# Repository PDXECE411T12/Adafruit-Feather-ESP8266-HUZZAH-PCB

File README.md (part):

<!DOCTYPE html>
<html lang="en" data-color-mode="light">
  <head>
    <meta charset="utf-8">
  <link rel="dns-prefetch" href="https://github.githubassets.com">
  <link rel="dns-prefetch" href="https://avatars0.githubusercontent.com">
  <link rel="dns-prefetch" href="https://avatars1.githubusercontent.com">
  <link rel="dns-prefetch" href="https://avatars2.githubusercontent.com">
  <link rel="dns-prefetch" href="https://avatars3.githubusercontent.com">
  <link rel="dns-prefetch" href="https://github-cloud.s3.amazonaws.com">
  <link rel="dns-prefetch" href="https://user-images.githubusercontent.com/">

  <link crossorigin="anonymous" media="all" integrity="sha512-BSy+E+S5PJuDWKcXiIXBoFJ7uJ+88y6hFdIhZpf7nf9MVNVvnJDPUaotaxFUQi8UXCLJOcGv1uifxVMc9o5DYQ==" rel="stylesheet" href="https://github.githubassets.com/assets/frameworks-052cbe13e4b93c9b8358a7178885c1a0.css" />
  
    <link crossorigin="anonymous" media="all" integrity="sha512-8Z+f0e6DBG9ZzxgV2Wf00KIGBotnuoKMOm3Rv8UbrIEoE7GWgF3QfZSZn6Mm4VUdBYSwqlvZLzeuQjojgH6lUA==" rel="stylesheet" href="https://github.githubassets.com/assets/github-f19f9fd1ee83046f59cf1815d967f4d0.css" />

  <script crossorigin="anonymous" defer="defer" integrity="sha512-8K2vvwbW+6H27Nad5ydg8PA2/aMD/LKq+EiK9s0U0hhVZxCI2tWBsYk9beAtisRw2j+Or5k2/F+6dk02nmj/PA==" type="application/javascript" src="https://github.githubassets.com/assets/environment-f0adafbf.js"></script>
    <script crossorigin="anonymous" defer="defer" integrity="sha512-gblEJf3YvaT1I3Ifn0J6OEL2Vgqq3zVla1fZ22EBfbdlAlq17e9EcuvE9InK3D/hrkh9kFJHDxGc7hXeetU45g==" type="application/javascript" src="https://github.githubassets.com/assets/chunk-frameworks-81b94425.js"></script>
    <script crossorigin="anonymous" defer="defer" integrity="sha512-TZfq2T+XE31Mcp17bGlABjjeQ/69IH2f/sBvS31c4Jua0e1O/NE+aVbQtItMM2GFlmeEm13p/zyyWGIx10jVKQ==" type="application/javascript" src="https://github.githubassets.com/assets/chunk-vendor-4d97ead9.js"></script>
  
  <script crossorigin="anonymous" defer="defer" integrity="sha512-r+GiAgjep5SyP+FNjsA/raxAAyrUmHUqN9sqy0T00pOb4D04zw6NLfs+JfGSukD34SO6nJq1KPuMyLVk36P3PA==" type="application/javascript" src="https://github.githubassets.com/assets/behaviors-afe1a202.js"></script>
  
    <script crossorigin="anonymous" defer="defer" integrity="sha512-xDmMfbDOi7C1qDeTcUUIjKfOAG5qhfSNSHRf7wT0crqnTCqtHlO1jBZmRSpjbpn4RyitzX75K0wQ/dpHqO/gAg==" type="application/javascript" data-module-id="./chunk-contributions-spider-graph.js" data-src="https://github.githubassets.com/assets/chunk-contributions-spider-graph-c4398c7d.js"></script>
    <script crossorigin="anonymous" defer="defer" integrity="sha512-obMR8mPKx8OvqRe34LgnUcxeJ1qujiA4ND3H6UX13ExMlA/WfHLjEzXRmgGRcRvN/8J1nzc+Z+jgz/PLTFy6zg==" type="application/javascript" data-module-id="./chunk-drag-drop.js" data-src="https://github.githubassets.com/assets/chunk-drag-drop-a1b311f2.js"></script>
    <script crossorigin="anonymous" defer="defer" integrity="sha512-JDXxclqmntAnHtqSwCjIe9M/W8XgzDvgCz4OuHGUBl2fcAN2rAXgRhw7eq1UA0wHiDw+4+lNAVTEeazYNQ4WSA==" type="application/javascript" data-module-id="./chunk-jump-to.js" data-src="https://github.githubassets.com/assets/chunk-jump-to-2435f172.js"></script>
    <script crossorigin="anonymous" defer="defer" integrity="sha512-scwzzcbKQ3b2bo4Y1BcFBMHXsT8F3fATHp7T1A/Zl3UAKEkJym7Gn1HSFHAKEEHbLO7j3q9U2S5VfYsHSgWXIw==" type="application/javascript" data-module-id="./chunk-lib.dev.js" data-src="https://github.githubassets.com/assets/chunk-lib.dev-b1cc33cd.js"></script>
    <script crossorigin="anonymous" defer="defer" integrity="sha512-tcH4xCRuMBAh1PruDaiwGnRIbHlF6bGLhxyCQ16uqok1cV5QFMguVPWJtN9KI0jGQOgN+Pha3+uOUXhXdfK/qw==" type="application/javascript" data-module-id="./chunk-profile-pins-element.js" data-src="https://github.githubassets.com/assets/chunk-profile-pins-element-b5c1f8c4.js"></script>
    <script crossorigin="anonymous" defer="defer" integrity="sha512-E+H+wAtjiqutBvn2cnXzDIvmasIhYiS7i7JzOfFUwo+Ej8zT54OrJtP//RhwixnypgOpCF4JvqzYy6zOtORDmg==" type="application/javascript" data-module-id="./chunk-runner-groups.js" data-src="https://github.githubassets.com/assets/chunk-runner-groups-13e1fec0.js"></script>
    <script crossorigin="anonymous" defer="defer" integrity="sha512-P4TJl8vmit2awffHeOfwscoWyj+xMvQBwQfL06P3Gy+5u9J9IYMgUJ4Ui+pbXNbJnAg6xQEZXUN4xk6PEGIrDg==" type="application/javascript" data-module-id="./chunk-sortable-behavior.js" data-src="https://github.githubassets.com/assets/chunk-sortable-behavior-3f84c997.js"></script>
    <script crossorigin="anonymous" defer="defer" integrity="sha512-ZBICwPA18KYIgHbafqdjnTkxoCSNf/39rTlupkrtdpIWizECoux0ROzjAgyAx20Bf27VfshuBqrYwDqOVftyag==" type="application/javascript" data-module-id="./chunk-tweetsodium.js" data-src="https://github.githubassets.com/assets/chunk-tweetsodium-641202c0.js"></script>
    <script crossorigin="anonymous" defer="defer" integrity="sha512-su8FOuJFv0H16y8vmT+N3HiFpDQnHKiLz/UEdGxlCfgwnKBy202gaBmkcBpqXigRg+A8pMDXcSPIWSEW+IIKvQ==" type="application/javascript" data-module-id="./chunk-user-status-submit.js" data-src="https://github.githubassets.com/assets/chunk-user-status-submit-b2ef053a.js"></script>
  
  <script crossorigin="anonymous" defer="defer" integrity="sha512-6L/yQAHVYWC71ORWOdwrq5FBI3reh2UxofwhL7r90SjgIzc6g4wk4QVsQ18qVWsUfVwJ9lF5sBTpcm8RPa4bzA==" type="application/javascript" src="https://github.githubassets.com/assets/repositories-e8bff240.js"></script>
<script crossorigin="anonymous" defer="defer" integrity="sha512-Ahh1vGV9jX7qzPdC1tA1y6PaLV9AbDPSlt2q8C7SUVVKTgoB5vDsUrKvaGh7Gj2Tv594XRcr0LjJdKA8HmL8iQ==" type="application/javascript" src="https://github.githubassets.com/assets/diffs-021875bc.js"></script>

  <meta name="viewport" content="width=device-width">
  
  <title>ECE411-RFID-Lock-Eagle/README.md at master · PDXECE411T12/ECE411-RFID-Lock-Eagle</title>
    <meta name="description" content="PCB files for the Adafruit Feather ESP8266 HUZZAH. Contribute to PDXECE411T12/ECE411-RFID-Lock-Eagle development by creating an account on GitHub.">
    <link rel="search" type="application/opensearchdescription+xml" href="/opensearch.xml" title="GitHub">
  <link rel="fluid-icon" href="https://github.com/fluidicon.png" title="GitHub">
  <meta property="fb:app_id" content="1401488693436528">
  <meta name="apple-itunes-app" content="app-id=1477376905" />
    <meta name="twitter:image:src" content="https://avatars1.githubusercontent.com/u/72583183?s=400&amp;v=4" /><meta name="twitter:site" content="@github" /><meta name="twitter:card" content="summary" /><meta name="twitter:title" content="PDXECE411T12/ECE411-RFID-Lock-Eagle" /><meta name="twitter:description" content="PCB files for the Adafruit Feather ESP8266 HUZZAH. Contribute to PDXECE411T12/ECE411-RFID-Lock-Eagle development by creating an account on GitHub." />
    <meta property="og:image" content="https://avatars1.githubusercontent.com/u/72583183?s=400&amp;v=4" /><meta property="og:site_name" content="GitHub" /><meta property="og:type" content="object" /><meta property="og:title" content="PDXECE411T12/ECE411-RFID-Lock-Eagle" /><meta property="og:url" content="https://github.com/PDXECE411T12/ECE411-RFID-Lock-Eagle" /><meta property="og:description" content="PCB files for the Adafruit Feather ESP8266 HUZZAH. Contribute to PDXECE411T12/ECE411-RFID-Lock-Eagle development by creating an account on GitHub." />

  <link rel="assets" href="https://github.githubassets.com/">
    <link rel="shared-web-socket" href="wss://alive.github.com/_sockets/u/11890817/ws?session=eyJ2IjoiVjMiLCJ1IjoxMTg5MDgxNywicyI6NjI4MzQzNTExLCJjIjoyNzYxNTY0MTg3LCJ0IjoxNjEwMTYxOTgzfQ==--c923629af6c32c08ffbedaf06c56a290086cc3c33050182d358216d3bba38706" data-refresh-url="/_alive">
    <link rel="shared-web-socket-src" href="/socket-worker-5029ae85.js">
  <link rel="sudo-modal" href="/sessions/sudo_modal">

  <meta name="request-id" content="CB8C:3913:354DAD:4B0690:5FF91F3B" data-pjax-transient="true" /><meta name="html-safe-nonce" content="bb28588b9a4154f45718a4b8536d0163a3f35f0025b7a8cbb5ef0c6285b8d703" data-pjax-transient="true" /><meta name="visitor-payload" content="eyJyZWZlcnJlciI6Imh0dHBzOi8vZ2l0aHViLmNvbS9QRFhFQ0U0MTFUMTIvRUNFNDExLVJGSUQtTG9jay1FYWdsZSIsInJlcXVlc3RfaWQiOiJDQjhDOjM5MTM6MzU0REFEOjRCMDY5MDo1RkY5MUYzQiIsInZpc2l0b3JfaWQiOiI4OTYxNzI5NTkyOTMxNTE1NTA3IiwicmVnaW9uX2VkZ2UiOiJzZWEiLCJyZWdpb25fcmVuZGVyIjoiaWFkIn0=" data-pjax-transient="true" /><meta name="visitor-hmac" content="5258440f105cfcba1c6f7d8f3d0d65e70d2235023c9c34c1e79f1a11475480ad" data-pjax-transient="true" />

    <meta name="hovercard-subject-tag" content="repository:310993614" data-pjax-transient>

  <meta name="github-keyboard-shortcuts" content="repository,source-code" data-pjax-transient="true" />

  <meta name="selected-link" value="repo_source" data-pjax-transient>

    <meta name="google-site-verification" content="c1kuD-K2HIVF635lypcsWPoD4kilo5-jA_wBFyT4uMY">
  <meta name="google-site-verification" content="KT5gs8h0wvaagLKAVWq8bbeNwnZZK1r1XQysX3xurLU">
  <meta name="google-site-verification" content="ZzhVyEFwb7w3e0-uOTltm8Jsck2F5StVihD0exw2fsA">
  <meta name="google-site-verification" content="GXs5KoUUkNCoaAZn7wPN-t01Pywp9M3sEjnt_3_ZWPc">

  <meta name="octolytics-host" content="collector.githubapp.com" /><meta name="octolytics-app-id" content="github" /><meta name="octolytics-event-url" content="https://collector.githubapp.com/github-external/browser_event" /><meta name="octolytics-actor-id" content="11890817" /><meta name="octolytics-actor-login" content="mhigginsmoy" /><meta name="octolytics-actor-hash" content="604e3ba3dde9b3fe24779cba42b193f28b9d92057d3e29f533aded6b62efa855" />

  <meta name="analytics-location" content="/&lt;user-name&gt;/&lt;repo-name&gt;/blob/show" data-pjax-transient="true" />

  <meta name="optimizely-datafile" content="{&quot;version&quot;: &quot;4&quot;, &quot;rollouts&quot;: [], &quot;typedAudiences&quot;: [], &quot;anonymizeIP&quot;: true, &quot;projectId&quot;: &quot;16737760170&quot;, &quot;variables&quot;: [], &quot;featureFlags&quot;: [], &quot;experiments&quot;: [], &quot;audiences&quot;: [{&quot;conditions&quot;: &quot;[\&quot;or\&quot;, {\&quot;match\&quot;: \&quot;exact\&quot;, \&quot;name\&quot;: \&quot;$opt_dummy_attribute\&quot;, \&quot;type\&quot;: \&quot;custom_attribute\&quot;, \&quot;value\&quot;: \&quot;$opt_dummy_value\&quot;}]&quot;, &quot;id&quot;: &quot;$opt_dummy_audience&quot;, &quot;name&quot;: &quot;Optimizely-Generated Audience for Backwards Compatibility&quot;}], &quot;groups&quot;: [], &quot;attributes&quot;: [{&quot;id&quot;: &quot;16822470375&quot;, &quot;key&quot;: &quot;user_id&quot;}, {&quot;id&quot;: &quot;17143601254&quot;, &quot;key&quot;: &quot;spammy&quot;}, {&quot;id&quot;: &quot;18175660309&quot;, &quot;key&quot;: &quot;organization_plan&quot;}, {&quot;id&quot;: &quot;18813001570&quot;, &quot;key&quot;: &quot;is_logged_in&quot;}, {&quot;id&quot;: &quot;19073851829&quot;, &quot;key&quot;: &quot;geo&quot;}], &quot;botFiltering&quot;: false, &quot;accountId&quot;: &quot;16737760170&quot;, &quot;events&quot;: [{&quot;experimentIds&quot;: [], &quot;id&quot;: &quot;17911811441&quot;, &quot;key&quot;: &quot;hydro_click.dashboard.teacher_toolbox_cta&quot;}, {&quot;experimentIds&quot;: [], &quot;id&quot;: &quot;18124116703&quot;, &quot;key&quot;: &quot;submit.organizations.complete_sign_up&quot;}, {&quot;experimentIds&quot;: [], &quot;id&quot;: &quot;18145892387&quot;, &quot;key&quot;: &quot;no_metric.tracked_outside_of_optimizely&quot;}, {&quot;experimentIds&quot;: [], &quot;id&quot;: &quot;18178755568&quot;, &quot;key&quot;: &quot;click.org_onboarding_checklist.add_repo&quot;}, {&quot;experimentIds&quot;: [], &quot;id&quot;: &quot;18180553241&quot;, &quot;key&quot;: &quot;submit.repository_imports.create&quot;}, {&quot;experimentIds&quot;: [], &quot;id&quot;: &quot;18186103728&quot;, &quot;key&quot;: &quot;click.help.learn_more_about_repository_creation&quot;}, {&quot;experimentIds&quot;: [], &quot;id&quot;: &quot;18188530140&quot;, &quot;key&quot;: &quot;test_event.do_not_use_in_production&quot;}, {&quot;experimentIds&quot;: [], &quot;id&quot;: &quot;18191963644&quot;, &quot;key&quot;: &quot;click.empty_org_repo_cta.transfer_repository&quot;}, {&quot;experimentIds&quot;: [], &quot;id&quot;: &quot;18195612788&quot;, &quot;key&quot;: &quot;click.empty_org_repo_cta.import_repository&quot;}, {&quot;experimentIds&quot;: [], &quot;id&quot;: &quot;18210945499&quot;, &quot;key&quot;: &quot;click.org_onboarding_checklist.invite_members&quot;}, {&quot;experimentIds&quot;: [], &quot;id&quot;: &quot;18211063248&quot;, &quot;key&quot;: &quot;click.empty_org_repo_cta.create_repository&quot;}, {&quot;experimentIds&quot;: [], &quot;id&quot;: &quot;18215721889&quot;, &quot;key&quot;: &quot;click.org_onboarding_checklist.update_profile&quot;}, {&quot;experimentIds&quot;: [], &quot;id&quot;: &quot;18224360785&quot;, &quot;key&quot;: &quot;click.org_onboarding_checklist.dismiss&quot;}, {&quot;experimentIds&quot;: [], &quot;id&quot;: &quot;18234832286&quot;, &quot;key&quot;: &quot;submit.organization_activation.complete&quot;}, {&quot;experimentIds&quot;: [], &quot;id&quot;: &quot;18252392383&quot;, &quot;key&quot;: &quot;submit.org_repository.create&quot;}, {&quot;experimentIds&quot;: [], &quot;id&quot;: &quot;18257551537&quot;, &quot;key&quot;: &quot;submit.org_member_invitation.create&quot;}, {&quot;experimentIds&quot;: [], &quot;id&quot;: &quot;18259522260&quot;, &quot;key&quot;: &quot;submit.organization_profile.update&quot;}, {&quot;experimentIds&quot;: [], &quot;id&quot;: &quot;18564603625&quot;, &quot;key&quot;: &quot;view.classroom_select_organization&quot;}, {&quot;experimentIds&quot;: [], &quot;id&quot;: &quot;18568612016&quot;, &quot;key&quot;: &quot;click.classroom_sign_in_click&quot;}, {&quot;experimentIds&quot;: [], &quot;id&quot;: &quot;18572592540&quot;, &quot;key&quot;: &quot;view.classroom_name&quot;}, {&quot;experimentIds&quot;: [], &quot;id&quot;: &quot;18574203855&quot;, &quot;key&quot;: &quot;click.classroom_create_organization&quot;}, {&quot;experimentIds&quot;: [], &quot;id&quot;: &quot;18582053415&quot;, &quot;key&quot;: &quot;click.classroom_select_organization&quot;}, {&quot;experimentIds&quot;: [], &quot;id&quot;: &quot;18589463420&quot;, &quot;key&quot;: &quot;click.classroom_create_classroom&quot;}, {&quot;experimentIds&quot;: [], &quot;id&quot;: &quot;18591323364&quot;, &quot;key&quot;: &quot;click.classroom_create_first_classroom&quot;}, {&quot;experimentIds&quot;: [], &quot;id&quot;: &quot;18591652321&quot;, &quot;key&quot;: &quot;click.classroom_grant_access&quot;}, {&quot;experimentIds&quot;: [], &quot;id&quot;: &quot;18607131425&quot;, &quot;key&quot;: &quot;view.classroom_creation&quot;}, {&quot;experimentIds&quot;: [], &quot;id&quot;: &quot;18831680583&quot;, &quot;key&quot;: &quot;upgrade_account_plan&quot;}, {&quot;experimentIds&quot;: [], &quot;id&quot;: &quot;19064064515&quot;, &quot;key&quot;: &quot;click.signup&quot;}, {&quot;experimentIds&quot;: [], &quot;id&quot;: &quot;19075373687&quot;, &quot;key&quot;: &quot;click.view_account_billing_page&quot;}, {&quot;experimentIds&quot;: [], &quot;id&quot;: &quot;19077355841&quot;, &quot;key&quot;: &quot;click.dismiss_signup_prompt&quot;}, {&quot;experimentIds&quot;: [], &quot;id&quot;: &quot;19079713938&quot;, &quot;key&quot;: &quot;click.contact_sales&quot;}, {&quot;experimentIds&quot;: [], &quot;id&quot;: &quot;19120963070&quot;, &quot;key&quot;: &quot;click.compare_account_plans&quot;}, {&quot;experimentIds&quot;: [], &quot;id&quot;: &quot;19151690317&quot;, &quot;key&quot;: &quot;click.upgrade_account_cta&quot;}, {&quot;experimentIds&quot;: [], &quot;id&quot;: &quot;19424193129&quot;, &quot;key&quot;: &quot;click.open_account_switcher&quot;}, {&quot;experimentIds&quot;: [], &quot;id&quot;: &quot;19520330825&quot;, &quot;key&quot;: &quot;click.visit_account_profile&quot;}, {&quot;experimentIds&quot;: [], &quot;id&quot;: &quot;19540970635&quot;, &quot;key&quot;: &quot;click.switch_account_context&quot;}], &quot;revision&quot;: &quot;390&quot;}" />
  <!-- To prevent page flashing, the optimizely JS needs to be loaded in the
    <head> tag before the DOM renders -->
  <script crossorigin="anonymous" defer="defer" integrity="sha512-VJrqSK702Mzl9EQxm2OvFxKaumGptgVdeJS2rsaLvVlOdR4HEu3ZFjtV83kMKdYRelUnxxaAFw0wthkpdEUafw==" type="application/javascript" src="https://github.githubassets.com/assets/optimizely-549aea48.js"></script>

      <meta name="hostname" content="github.com">
    <meta name="user-login" content="mhigginsmoy">

      <meta name="expected-hostname" content="github.com">

      <meta name="js-proxy-site-detection-payload" content="MGVlMGNhZGI4ZmVkOWFlMWMwZDgzMzQyODBiZWVlYjYzMjVkZTUxYzQwODdkNWZmZTdkODFmOWNhOGYyZGZjZXx7InJlbW90ZV9hZGRyZXNzIjoiOTcuMTE1LjE0My4yMjgiLCJyZXF1ZXN0X2lkIjoiQ0I4QzozOTEzOjM1NERBRDo0QjA2OTA6NUZGOTFGM0IiLCJ0aW1lc3RhbXAiOjE2MTAxNjE5ODMsImhvc3QiOiJnaXRodWIuY29tIn0=">

    <meta name="enabled-features" content="MARKETPLACE_PENDING_INSTALLATIONS,JS_HTTP_CACHE_HEADERS,ACTIONS_ENVIRONMENTS,ACTIONS_ENVIRONMENTS,TASK_LIST_AUTOCOMPLETE,MULTI_WORD_SUGGESTER">

  <meta http-equiv="x-pjax-version" content="dbd3fad76a569cdeb65e5d61501f8285423ed387758f5ff64d90c6c4eaca85ca">

        <link href="https://github.com/PDXECE411T12/ECE411-RFID-Lock-Eagle/commits/master.atom" rel="alternate" title="Recent Commits to ECE411-RFID-Lock-Eagle:master" type="application/atom+xml">

  <meta name="go-import" content="github.com/PDXECE411T12/ECE411-RFID-Lock-Eagle git https://github.com/PDXECE411T12/ECE411-RFID-Lock-Eagle.git">

  <meta name="octolytics-dimension-user_id" content="72583183" /><meta name="octolytics-dimension-user_login" content="PDXECE411T12" /><meta name="octolytics-dimension-repository_id" content="310993614" /><meta name="octolytics-dimension-repository_nwo" content="PDXECE411T12/ECE411-RFID-Lock-Eagle" /><meta name="octolytics-dimension-repository_public" content="true" /><meta name="octolytics-dimension-repository_is_fork" content="true" /><meta name="octolytics-dimension-repository_parent_id" content="53283869" /><meta name="octolytics-dimension-repository_parent_nwo" content="adafruit/Adafruit-Feather-ESP8266-HUZZAH-PCB" /><meta name="octolytics-dimension-repository_network_root_id" content="53283869" /><meta name="octolytics-dimension-repository_network_root_nwo" content="adafruit/Adafruit-Feather-ESP8266-HUZZAH-PCB" /><meta name="octolytics-dimension-repository_explore_github_marketplace_ci_cta_shown" content="true" />

    <link rel="canonical" href="https://github.com/PDXECE411T12/ECE411-RFID-Lock-Eagle/blob/master/README.md" data-pjax-transient>

  <meta name="browser-stats-url" content="https://api.github.com/_private/browser/stats">

  <meta name="browser-errors-url" content="https://api.github.com/_private/browser/errors">

  <meta name="browser-optimizely-client-errors-url" content="https://api.github.com/_private/browser/optimizely_client/errors">

  <link rel="mask-icon" href="https://github.githubassets.com/pinned-octocat.svg" color="#000000">
  <link rel="alternate icon" class="js-site-favicon" type="image/png" href="https://github.githubassets.com/favicons/favicon.png">
  <link rel="icon" class="js-site-favicon" type="image/svg+xml" href="https://github.githubassets.com/favicons/favicon.svg">

<meta name="theme-color" content="#1e2327">
    <meta name="color-scheme" content="light dark">

  <link rel="manifest" href="/manifest.json" crossOrigin="use-credentials">

  </head>

  <body class="logged-in env-production page-responsive page-blob">

    <div class="position-relative js-header-wrapper ">
      <a href="#start-of-content" class="p-3 bg-blue text-white show-on-focus js-skip-to-content">Skip to content</a>
      <span class="progress-pjax-loader width-full js-pjax-loader-bar Progress position-fixed">
    <span style="background-color: #79b8ff;width: 0%;" class="Progress-item progress-pjax-loader-bar "></span>
</span>      

            <header class="Header js-details-container Details px-3 px-md-4 px-lg-5 flex-wrap flex-md-nowrap" role="banner" >
    <div class="Header-item mt-n1 mb-n1  d-none d-md-flex">
      <a class="Header-link " href="https://github.com/" data-hotkey="g d"
  aria-label="Homepage " data-ga-click="Header, go to dashboard, icon:logo">
  <svg class="octicon octicon-mark-github v-align-middle" height="32" viewBox="0 0 16 16" version="1.1" width="32" aria-hidden="true"><path fill-rule="evenodd" d="M8 0C3.58 0 0 3.58 0 8c0 3.54 2.29 6.53 5.47 7.59.4.07.55-.17.55-.38 0-.19-.01-.82-.01-1.49-2.01.37-2.53-.49-2.69-.94-.09-.23-.48-.94-.82-1.13-.28-.15-.68-.52-.01-.53.63-.01 1.08.58 1.23.82.72 1.21 1.87.87 2.33.66.07-.52.28-.87.51-1.07-1.78-.2-3.64-.89-3.64-3.95 0-.87.31-1.59.82-2.15-.08-.2-.36-1.02.08-2.12 0 0 .67-.21 2.2.82.64-.18 1.32-.27 2-.27.68 0 1.36.09 2 .27 1.53-1.04 2.2-.82 2.2-.82.44 1.1.16 1.92.08 2.12.51.56.82 1.27.82 2.15 0 3.07-1.87 3.75-3.65 3.95.29.25.54.73.54 1.48 0 1.07-.01 1.93-.01 2.2 0 .21.15.46.55.38A8.013 8.013 0 0016 8c0-4.42-3.58-8-8-8z"></path></svg>
</a>

    </div>

    <div class="Header-item d-md-none">
      <button class="Header-link btn-link js-details-target" type="button" aria-label="Toggle navigation" aria-expanded="false">
        <svg height="24" class="octicon octicon-three-bars" viewBox="0 0 16 16" version="1.1" width="24" aria-hidden="true"><path fill-rule="evenodd" d="M1 2.75A.75.75 0 011.75 2h12.5a.75.75 0 110 1.5H1.75A.75.75 0 011 2.75zm0 5A.75.75 0 011.75 7h12.5a.75.75 0 110 1.5H1.75A.75.75 0 011 7.75zM1.75 12a.75.75 0 100 1.5h12.5a.75.75 0 100-1.5H1.75z"></path></svg>
      </button>
    </div>

    <div class="Header-item Header-item--full flex-column flex-md-row width-full flex-order-2 flex-md-order-none mr-0 mr-md-3 mt-3 mt-md-0 Details-content--hidden-not-important d-md-flex">
          <div class="header-search flex-auto js-site-search position-relative flex-self-stretch flex-md-self-auto mb-3 mb-md-0 mr-0 mr-md-3 scoped-search site-scoped-search js-jump-to"
  role="combobox"
  aria-owns="jump-to-results"
  aria-label="Search or jump to"
  aria-haspopup="listbox"
  aria-expanded="false"
>
  <div class="position-relative">
    <!-- '"` --><!-- </textarea></xmp> --></option></form><form class="js-site-search-form" role="search" aria-label="Site" data-flagged-in="true" data-scope-type="Repository" data-scope-id="310993614" data-scoped-search-url="/PDXECE411T12/ECE411-RFID-Lock-Eagle/search" data-owner-scoped-search-url="/orgs/PDXECE411T12/search" data-unscoped-search-url="/search" action="/PDXECE411T12/ECE411-RFID-Lock-Eagle/search" accept-charset="UTF-8" method="get">
      <label class="form-control input-sm header-search-wrapper p-0 js-chromeless-input-container header-search-wrapper-jump-to position-relative d-flex flex-justify-between flex-items-center">
        <input type="text"
          class="form-control input-sm header-search-input jump-to-field js-jump-to-field js-site-search-focus js-site-search-field is-clearable"
          data-hotkey="s,/"
          name="q"
          value=""
          placeholder="Search or jump to…"
          data-unscoped-placeholder="Search or jump to…"
          data-scoped-placeholder="Search or jump to…"
          autocapitalize="off"
          aria-autocomplete="list"
          aria-controls="jump-to-results"
          aria-label="Search or jump to…"
          data-jump-to-suggestions-path="/_graphql/GetSuggestedNavigationDestinations"
          spellcheck="false"
          autocomplete="off"
          >
          <input type="hidden" value="dME4aXFkwmm5Rvf+kk1gJ66kkKNDXJhfK65a4VIdA7DzH37Iv1GtaxmqYMjaGNKyUzW+3UWV6cWrZOmQsolpLg==" data-csrf="true" class="js-data-jump-to-suggestions-path-csrf" />
          <input type="hidden" class="js-site-search-type-field" name="type" >

            <div class="Box position-absolute overflow-hidden d-none jump-to-suggestions js-jump-to-suggestions-container">
              
<ul class="d-none js-jump-to-suggestions-template-container">

<li class="d-flex flex-justify-start flex-items-center p-0 f5 navigation-item js-navigation-item js-jump-to-suggestion" role="option">
  <a tabindex="-1" class="no-underline d-flex flex-auto flex-items-center jump-to-suggestions-path js-jump-to-suggestion-path js-navigation-open p-2" href="" data-item-type="suggestion">
    <div class="jump-to-octicon js-jump-to-octicon flex-shrink-0 mr-2 text-center d-none">
      <svg height="16" width="16" class="octicon octicon-repo flex-shrink-0 js-jump-to-octicon-repo d-none" title="Repository" aria-label="Repository" viewBox="0 0 16 16" version="1.1" role="img"><path fill-rule="evenodd" d="M2 2.5A2.5 2.5 0 014.5 0h8.75a.75.75 0 01.75.75v12.5a.75.75 0 01-.75.75h-2.5a.75.75 0 110-1.5h1.75v-2h-8a1 1 0 00-.714 1.7.75.75 0 01-1.072 1.05A2.495 2.495 0 012 11.5v-9zm10.5-1V9h-8c-.356 0-.694.074-1 .208V2.5a1 1 0 011-1h8zM5 12.25v3.25a.25.25 0 00.4.2l1.45-1.087a.25.25 0 01.3 0L8.6 15.7a.25.25 0 00.4-.2v-3.25a.25.25 0 00-.25-.25h-3.5a.25.25 0 00-.25.25z"></path></svg>
      <svg height="16" width="16" class="octicon octicon-project flex-shrink-0 js-jump-to-octicon-project d-none" title="Project" aria-label="Project" viewBox="0 0 16 16" version="1.1" role="img"><path fill-rule="evenodd" d="M1.75 0A1.75 1.75 0 000 1.75v12.5C0 15.216.784 16 1.75 16h12.5A1.75 1.75 0 0016 14.25V1.75A1.75 1.75 0 0014.25 0H1.75zM1.5 1.75a.25.25 0 01.25-.25h12.5a.25.25 0 01.25.25v12.5a.25.25 0 01-.25.25H1.75a.25.25 0 01-.25-.25V1.75zM11.75 3a.75.75 0 00-.75.75v7.5a.75.75 0 001.5 0v-7.5a.75.75 0 00-.75-.75zm-8.25.75a.75.75 0 011.5 0v5.5a.75.75 0 01-1.5 0v-5.5zM8 3a.75.75 0 00-.75.75v3.5a.75.75 0 001.5 0v-3.5A.75.75 0 008 3z"></path></svg>
      <svg height="16" width="16" class="octicon octicon-search flex-shrink-0 js-jump-to-octicon-search d-none" title="Search" aria-label="Search" viewBox="0 0 16 16" version="1.1" role="img"><path fill-rule="evenodd" d="M11.5 7a4.499 4.499 0 11-8.998 0A4.499 4.499 0 0111.5 7zm-.82 4.74a6 6 0 111.06-1.06l3.04 3.04a.75.75 0 11-1.06 1.06l-3.04-3.04z"></path></svg>
    </div>

    <div class="jump-to-suggestion-name js-jump-to-suggestion-name flex-auto overflow-hidden text-left no-wrap css-truncate css-truncate-target">
    </div>

    <div class="border rounded-1 flex-shrink-0 bg-gray px-1 text-gray-light ml-1 f6 d-none js-jump-to-badge-search">
      <span class="js-jump-to-badge-search-text-default d-none" aria-label="in this repository">
        In this repository
      </span>
      <span class="js-jump-to-badge-search-text-global d-none" aria-label="in all of GitHub">
        All GitHub
      </span>
      <span aria-hidden="true" class="d-inline-block ml-1 v-align-middle">↵</span>
    </div>

    <div aria-hidden="true" class="border rounded-1 flex-shrink-0 bg-gray px-1 text-gray-light ml-1 f6 d-none d-on-nav-focus js-jump-to-badge-jump">
      Jump to
      <span class="d-inline-block ml-1 v-align-middle">↵</span>
    </div>
  </a>
</li>

</ul>

<ul class="d-none js-jump-to-no-results-template-container">
  <li class="d-flex flex-justify-center flex-items-center f5 d-none js-jump-to-suggestion p-2">
    <span class="text-gray">No suggested jump to results</span>
  </li>
</ul>

<ul id="jump-to-results" role="listbox" class="p-0 m-0 js-navigation-container jump-to-suggestions-results-container js-jump-to-suggestions-results-container">

<li class="d-flex flex-justify-start flex-items-center p-0 f5 navigation-item js-navigation-item js-jump-to-scoped-search d-none" role="option">
  <a tabindex="-1" class="no-underline d-flex flex-auto flex-items-center jump-to-suggestions-path js-jump-to-suggestion-path js-navigation-open p-2" href="" data-item-type="scoped_search">
    <div class="jump-to-octicon js-jump-to-octicon flex-shrink-0 mr-2 text-center d-none">
      <svg height="16" width="16" class="octicon octicon-repo flex-shrink-0 js-jump-to-octicon-repo d-none" title="Repository" aria-label="Repository" viewBox="0 0 16 16" version="1.1" role="img"><path fill-rule="evenodd" d="M2 2.5A2.5 2.5 0 014.5 0h8.75a.75.75 0 01.75.75v12.5a.75.75 0 01-.75.75h-2.5a.75.75 0 110-1.5h1.75v-2h-8a1 1 0 00-.714 1.7.75.75 0 01-1.072 1.05A2.495 2.495 0 012 11.5v-9zm10.5-1V9h-8c-.356 0-.694.074-1 .208V2.5a1 1 0 011-1h8zM5 12.25v3.25a.25.25 0 00.4.2l1.45-1.087a.25.25 0 01.3 0L8.6 15.7a.25.25 0 00.4-.2v-3.25a.25.25 0 00-.25-.25h-3.5a.25.25 0 00-.25.25z"></path></svg>
      <svg height="16" width="16" class="octicon octicon-project flex-shrink-0 js-jump-to-octicon-project d-none" title="Project" aria-label="Project" viewBox="0 0 16 16" version="1.1" role="img"><path fill-rule="evenodd" d="M1.75 0A1.75 1.75 0 000 1.75v12.5C0 15.216.784 16 1.75 16h12.5A1.75 1.75 0 0016 14.25V1.75A1.75 1.75 0 0014.25 0H1.75zM1.5 1.75a.25.25 0 01.25-.25h12.5a.25.25 0 01.25.25v12.5a.25.25 0 01-.25.25H1.75a.25.25 0 01-.25-.25V1.75zM11.75 3a.75.75 0 00-.75.75v7.5a.75.75 0 001.5 0v-7.5a.75.75 0 00-.75-.75zm-8.25.75a.75.75 0 011.5 0v5.5a.75.75 0 01-1.5 0v-5.5zM8 3a.75.75 0 00-.75.75v3.5a.75.75 0 001.5 0v-3.5A.75.75 0 008 3z"></path></svg>
      <svg height="16" width="16" class="octicon octicon-search flex-shrink-0 js-jump-to-octicon-search d-none" title="Search" aria-label="Search" viewBox="0 0 16 16" version="1.1" role="img"><path fill-rule="evenodd" d="M11.5 7a4.499 4.499 0 11-8.998 0A4.499 4.499 0 0111.5 7zm-.82 4.74a6 6 0 111.06-1.06l3.04 3.04a.75.75 0 11-1.06 1.06l-3.04-3.04z"></path></svg>
    </div>

    <div class="jump-to-suggestion-name js-jump-to-suggestion-name flex-auto overflow-hidden text-left no-wrap css-truncate css-truncate-target">
    </div>

    <div class="border rounded-1 flex-shrink-0 bg-gray px-1 text-gray-light ml-1 f6 d-none js-jump-to-badge-search">
      <span class="js-jump-to-badge-search-text-default d-none" aria-label="in this repository">
        In this repository
      </span>
      <span class="js-jump-to-badge-search-text-global d-none" aria-label="in all of GitHub">
        All GitHub
      </span>
      <span aria-hidden="true" class="d-inline-block ml-1 v-align-middle">↵</span>
    </div>

    <div aria-hidden="true" class="border rounded-1 flex-shrink-0 bg-gray px-1 text-gray-light ml-1 f6 d-none d-on-nav-focus js-jump-to-badge-jump">
      Jump to
      <span class="d-inline-block ml-1 v-align-middle">↵</span>
    </div>
  </a>
</li>

<li class="d-flex flex-justify-start flex-items-center p-0 f5 navigation-item js-navigation-item js-jump-to-owner-scoped-search d-none" role="option">
  <a tabindex="-1" class="no-underline d-flex flex-auto flex-items-center jump-to-suggestions-path js-jump-to-suggestion-path js-navigation-open p-2" href="" data-item-type="owner_scoped_search">
    <div class="jump-to-octicon js-jump-to-octicon flex-shrink-0 mr-2 text-center d-none">
      <svg height="16" width="16" class="octicon octicon-repo flex-shrink-0 js-jump-to-octicon-repo d-none" title="Repository" aria-label="Repository" viewBox="0 0 16 16" version="1.1" role="img"><path fill-rule="evenodd" d="M2 2.5A2.5 2.5 0 014.5 0h8.75a.75.75 0 01.75.75v12.5a.75.75 0 01-.75.75h-2.5a.75.75 0 110-1.5h1.75v-2h-8a1 1 0 00-.714 1.7.75.75 0 01-1.072 1.05A2.495 2.495 0 012 11.5v-9zm10.5-1V9h-8c-.356 0-.694.074-1 .208V2.5a1 1 0 011-1h8zM5 12.25v3.25a.25.25 0 00.4.2l1.45-1.087a.25.25 0 01.3 0L8.6 15.7a.25.25 0 00.4-.2v-3.25a.25.25 0 00-.25-.25h-3.5a.25.25 0 00-.25.25z"></path></svg>
      <svg height="16" width="16" class="octicon octicon-project flex-shrink-0 js-jump-to-octicon-project d-none" title="Project" aria-label="Project" viewBox="0 0 16 16" version="1.1" role="img"><path fill-rule="evenodd" d="M1.75 0A1.75 1.75 0 000 1.75v12.5C0 15.216.784 16 1.75 16h12.5A1.75 1.75 0 0016 14.25V1.75A1.75 1.75 0 0014.25 0H1.75zM1.5 1.75a.25.25 0 01.25-.25h12.5a.25.25 0 01.25.25v12.5a.25.25 0 01-.25.25H1.75a.25.25 0 01-.25-.25V1.75zM11.75 3a.75.75 0 00-.75.75v7.5a.75.75 0 001.5 0v-7.5a.75.75 0 00-.75-.75zm-8.25.75a.75.75 0 011.5 0v5.5a.75.75 0 01-1.5 0v-5.5zM8 3a.75.75 0 00-.75.75v3.5a.75.75 0 001.5 0v-3.5A.75.75 0 008 3z"></path></svg>
      <svg height="16" width="16" class="octicon octicon-search flex-shrink-0 js-jump-to-octicon-search d-none" title="Search" aria-label="Search" viewBox="0 0 16 16" version="1.1" role="img"><path fill-rule="evenodd" d="M11.5 7a4.499 4.499 0 11-8.998 0A4.499 4.499 0 0111.5 7zm-.82 4.74a6 6 0 111.06-1.06l3.04 3.04a.75.75 0 11-1.06 1.06l-3.04-3.04z"></path></svg>
    </div>

    <div class="jump-to-suggestion-name js-jump-to-suggestion-name flex-auto overflow-hidden text-left no-wrap css-truncate css-truncate-target">
    </div>

    <div class="border rounded-1 flex-shrink-0 bg-gray px-1 text-gray-light ml-1 f6 d-none js-jump-to-badge-search">
      <span class="js-jump-to-badge-search-text-default d-none" aria-label="in this organization">
        In this organization
      </span>
      <span class="js-jump-to-badge-search-text-global d-none" aria-label="in all of GitHub">
        All GitHub
      </span>
      <span aria-hidden="true" class="d-inline-block ml-1 v-align-middle">↵</span>
    </div>

    <div aria-hidden="true" class="border rounded-1 flex-shrink-0 bg-gray px-1 text-gray-light ml-1 f6 d-none d-on-nav-focus js-jump-to-badge-jump">
      Jump to
      <span class="d-inline-block ml-1 v-align-middle">↵</span>
    </div>
  </a>
</li>

<li class="d-flex flex-justify-start flex-items-center p-0 f5 navigation-item js-navigation-item js-jump-to-global-search d-none" role="option">
  <a tabindex="-1" class="no-underline d-flex flex-auto flex-items-center jump-to-suggestions-path js-jump-to-suggestion-path js-navigation-open p-2" href="" data-item-type="global_search">
    <div class="jump-to-octicon js-jump-to-octicon flex-shrink-0 mr-2 text-center d-none">
      <svg height="16" width="16" class="octicon octicon-repo flex-shrink-0 js-jump-to-octicon-repo d-none" title="Repository" aria-label="Repository" viewBox="0 0 16 16" version="1.1" role="img"><path fill-rule="evenodd" d="M2 2.5A2.5 2.5 0 014.5 0h8.75a.75.75 0 01.75.75v12.5a.75.75 0 01-.75.75h-2.5a.75.75 0 110-1.5h1.75v-2h-8a1 1 0 00-.714 1.7.75.75 0 01-1.072 1.05A2.495 2.495 0 012 11.5v-9zm10.5-1V9h-8c-.356 0-.694.074-1 .208V2.5a1 1 0 011-1h8zM5 12.25v3.25a.25.25 0 00.4.2l1.45-1.087a.25.25 0 01.3 0L8.6 15.7a.25.25 0 00.4-.2v-3.25a.25.25 0 00-.25-.25h-3.5a.25.25 0 00-.25.25z"></path></svg>
      <svg height="16" width="16" class="octicon octicon-project flex-shrink-0 js-jump-to-octicon-project d-none" title="Project" aria-label="Project" viewBox="0 0 16 16" version="1.1" role="img"><path fill-rule="evenodd" d="M1.75 0A1.75 1.75 0 000 1.75v12.5C0 15.216.784 16 1.75 16h12.5A1.75 1.75 0 0016 14.25V1.75A1.75 1.75 0 0014.25 0H1.75zM1.5 1.75a.25.25 0 01.25-.25h12.5a.25.25 0 01.25.25v12.5a.25.25 0 01-.25.25H1.75a.25.25 0 01-.25-.25V1.75zM11.75 3a.75.75 0 00-.75.75v7.5a.75.75 0 001.5 0v-7.5a.75.75 0 00-.75-.75zm-8.25.75a.75.75 0 011.5 0v5.5a.75.75 0 01-1.5 0v-5.5zM8 3a.75.75 0 00-.75.75v3.5a.75.75 0 001.5 0v-3.5A.75.75 0 008 3z"></path></svg>
      <svg height="16" width="16" class="octicon octicon-search flex-shrink-0 js-jump-to-octicon-search d-none" title="Search" aria-label="Search" viewBox="0 0 16 16" version="1.1" role="img"><path fill-rule="evenodd" d="M11.5 7a4.499 4.499 0 11-8.998 0A4.499 4.499 0 0111.5 7zm-.82 4.74a6 6 0 111.06-1.06l3.04 3.04a.75.75 0 11-1.06 1.06l-3.04-3.04z"></path></svg>
    </div>

    <div class="jump-to-suggestion-name js-jump-to-suggestion-name flex-auto overflow-hidden text-left no-wrap css-truncate css-truncate-target">
    </div>

    <div class="border rounded-1 flex-shrink-0 bg-gray px-1 text-gray-light ml-1 f6 d-none js-jump-to-badge-search">
      <span class="js-jump-to-badge-search-text-default d-none" aria-label="in this repository">
        In this repository
      </span>
      <span class="js-jump-to-badge-search-text-global d-none" aria-label="in all of GitHub">
        All GitHub
      </span>
      <span aria-hidden="true" class="d-inline-block ml-1 v-align-middle">↵</span>
    </div>

    <div aria-hidden="true" class="border rounded-1 flex-shrink-0 bg-gray px-1 text-gray-light ml-1 f6 d-none d-on-nav-focus js-jump-to-badge-jump">
      Jump to
      <span class="d-inline-block ml-1 v-align-middle">↵</span>
    </div>
  </a>
</li>

    <li class="d-flex flex-justify-center flex-items-center p-0 f5 js-jump-to-suggestion">
      <svg viewBox="0 0 16 16" fill="none" style="box-sizing: content-box; color: var(--color-icon-primary);" class="m-3" width="32" height="32">
  <circle cx="8" cy="8" r="7" stroke="currentColor" stroke-opacity="0.25" stroke-width="2" vector-effect="non-scaling-stroke" />
  <path d="M15 8a7.002 7.002 0 00-7-7" stroke="currentColor" stroke-width="2" stroke-linecap="round" vector-effect="non-scaling-stroke">
    <animateTransform attributeName="transform" type="rotate" from="0 8 8" to="360 8 8" dur="1s" repeatCount="indefinite" />
  </path>
</svg>
    </li>
</ul>

            </div>
      </label>
</form>  </div>
</div>

        <nav class="d-flex flex-column flex-md-row flex-self-stretch flex-md-self-auto" aria-label="Global">
      <a class="Header-link py-md-3 d-block d-md-none py-2 border-top border-md-top-0 border-white-fade-15" data-ga-click="Header, click, Nav menu - item:dashboard:user" aria-label="Dashboard" href="/dashboard">
        Dashboard
</a>
    <a class="js-selected-navigation-item Header-link mt-md-n3 mb-md-n3 py-2 py-md-3 mr-0 mr-md-3 border-top border-md-top-0 border-white-fade-15" data-hotkey="g p" data-ga-click="Header, click, Nav menu - item:pulls context:user" aria-label="Pull requests you created" data-selected-links="/pulls /pulls/assigned /pulls/mentioned /pulls" href="/pulls">
        Pull<span class="d-inline d-md-none d-lg-inline"> request</span>s
</a>
    <a class="js-selected-navigation-item Header-link mt-md-n3 mb-md-n3 py-2 py-md-3 mr-0 mr-md-3 border-top border-md-top-0 border-white-fade-15" data-hotkey="g i" data-ga-click="Header, click, Nav menu - item:issues context:user" aria-label="Issues you created" data-selected-links="/issues /issues/assigned /issues/mentioned /issues" href="/issues">
      Issues
</a>

      <div class="d-flex position-relative">
        <a class="js-selected-navigation-item Header-link flex-auto mt-md-n3 mb-md-n3 py-2 py-md-3 mr-0 mr-md-3 border-top border-md-top-0 border-white-fade-15" data-ga-click="Header, click, Nav menu - item:marketplace context:user" data-octo-click="marketplace_click" data-octo-dimensions="location:nav_bar" data-selected-links=" /marketplace" href="/marketplace">
          Marketplace
</a>      </div>

    <a class="js-selected-navigation-item Header-link mt-md-n3 mb-md-n3 py-2 py-md-3 mr-0 mr-md-3 border-top border-md-top-0 border-white-fade-15" data-ga-click="Header, click, Nav menu - item:explore" data-selected-links="/explore /trending /trending/developers /integrations /integrations/feature/code /integrations/feature/collaborate /integrations/feature/ship showcases showcases_search showcases_landing /explore" href="/explore">
      Explore
</a>

    <a class="Header-link d-block d-md-none mr-0 mr-md-3 py-2 py-md-3 border-top border-md-top-0 border-white-fade-15" href="/settings/profile">
      Settings
</a>
    <a class="Header-link d-block d-md-none mr-0 mr-md-3 py-2 py-md-3 border-top border-md-top-0 border-white-fade-15" href="/mhigginsmoy">
      
      mhigginsmoy
</a>
    <!-- '"` --><!-- </textarea></xmp> --></option></form><form action="/logout" accept-charset="UTF-8" method="post"><input type="hidden" name="authenticity_token" value="i7JOgaQgxykYBN6POYslENM/e6z3DRvtK2EYQ36IDwJEUItU5jJPeunRtLUgMT2jUNuHqoS5vgNbhSIPv/q8Mw==" />
      <button type="submit" class="Header-link mr-0 mr-md-3 py-2 py-md-3 border-top border-md-top-0 border-white-fade-15 d-md-none btn-link d-block width-full text-left" data-ga-click="Header, sign out, icon:logout" style="padding-left: 2px;">
        <svg class="octicon octicon-sign-out v-align-middle" viewBox="0 0 16 16" version="1.1" width="16" height="16" aria-hidden="true"><path fill-rule="evenodd" d="M2 2.75C2 1.784 2.784 1 3.75 1h2.5a.75.75 0 010 1.5h-2.5a.25.25 0 00-.25.25v10.5c0 .138.112.25.25.25h2.5a.75.75 0 010 1.5h-2.5A1.75 1.75 0 012 13.25V2.75zm10.44 4.5H6.75a.75.75 0 000 1.5h5.69l-1.97 1.97a.75.75 0 101.06 1.06l3.25-3.25a.75.75 0 000-1.06l-3.25-3.25a.75.75 0 10-1.06 1.06l1.97 1.97z"></path></svg>
        Sign out
      </button>
</form></nav>

    </div>

    <div class="Header-item Header-item--full flex-justify-center d-md-none position-relative">
        <a class="Header-link " href="https://github.com/" data-hotkey="g d"
  aria-label="Homepage " data-ga-click="Header, go to dashboard, icon:logo">
  <svg class="octicon octicon-mark-github v-align-middle" height="32" viewBox="0 0 16 16" version="1.1" width="32" aria-hidden="true"><path fill-rule="evenodd" d="M8 0C3.58 0 0 3.58 0 8c0 3.54 2.29 6.53 5.47 7.59.4.07.55-.17.55-.38 0-.19-.01-.82-.01-1.49-2.01.37-2.53-.49-2.69-.94-.09-.23-.48-.94-.82-1.13-.28-.15-.68-.52-.01-.53.63-.01 1.08.58 1.23.82.72 1.21 1.87.87 2.33.66.07-.52.28-.87.51-1.07-1.78-.2-3.64-.89-3.64-3.95 0-.87.31-1.59.82-2.15-.08-.2-.36-1.02.08-2.12 0 0 .67-.21 2.2.82.64-.18 1.32-.27 2-.27.68 0 1.36.09 2 .27 1.53-1.04 2.2-.82 2.2-.82.44 1.1.16 1.92.08 2.12.51.56.82 1.27.82 2.15 0 3.07-1.87 3.75-3.65 3.95.29.25.54.73.54 1.48 0 1.07-.01 1.93-.01 2.2 0 .21.15.46.55.38A8.013 8.013 0 0016 8c0-4.42-3.58-8-8-8z"></path></svg>
</a>

    </div>

    <div class="Header-item mr-0 mr-md-3 flex-order-1 flex-md-order-none">

    <notification-indicator class="js-socket-channel" data-channel="eyJjIjoibm90aWZpY2F0aW9uLWNoYW5nZWQ6MTE4OTA4MTciLCJ0IjoxNjEwMTYxOTgzfQ==--3a3421eb255fd870444641eb4ac0889615d9ada94d0632c3d7128237a7b10412">
      <a href="/notifications"
         class="Header-link notification-indicator position-relative tooltipped tooltipped-sw"
         
         aria-label="You have no unread notifications"
         data-hotkey="g n"
         data-ga-click="Header, go to notifications, icon:read"
         data-target="notification-indicator.link">
         <span class="mail-status  " data-target="notification-indicator.modifier"></span>
         <svg class="octicon octicon-bell" viewBox="0 0 16 16" version="1.1" width="16" height="16" aria-hidden="true"><path d="M8 16a2 2 0 001.985-1.75c.017-.137-.097-.25-.235-.25h-3.5c-.138 0-.252.113-.235.25A2 2 0 008 16z"></path><path fill-rule="evenodd" d="M8 1.5A3.5 3.5 0 004.5 5v2.947c0 .346-.102.683-.294.97l-1.703 2.556a.018.018 0 00-.003.01l.001.006c0 .002.002.004.004.006a.017.017 0 00.006.004l.007.001h10.964l.007-.001a.016.016 0 00.006-.004.016.016 0 00.004-.006l.001-.007a.017.017 0 00-.003-.01l-1.703-2.554a1.75 1.75 0 01-.294-.97V5A3.5 3.5 0 008 1.5zM3 5a5 5 0 0110 0v2.947c0 .05.015.098.042.139l1.703 2.555A1.518 1.518 0 0113.482 13H2.518a1.518 1.518 0 01-1.263-2.36l1.703-2.554A.25.25 0 003 7.947V5z"></path></svg>
      </a>
    </notification-indicator>

    </div>

    <div class="Header-item position-relative d-none d-md-flex">
        <details class="details-overlay details-reset">
  <summary class="Header-link"
      aria-label="Create new…"
      data-ga-click="Header, create new, icon:add">
      <svg class="octicon octicon-plus" viewBox="0 0 16 16" version="1.1" width="16" height="16" aria-hidden="true"><path fill-rule="evenodd" d="M7.75 2a.75.75 0 01.75.75V7h4.25a.75.75 0 110 1.5H8.5v4.25a.75.75 0 11-1.5 0V8.5H2.75a.75.75 0 010-1.5H7V2.75A.75.75 0 017.75 2z"></path></svg> <span class="dropdown-caret"></span>
  </summary>
  <details-menu class="dropdown-menu dropdown-menu-sw">
    
<a role="menuitem" class="dropdown-item" href="/new" data-ga-click="Header, create new repository">
  New repository
</a>

  <a role="menuitem" class="dropdown-item" href="/new/import" data-ga-click="Header, import a repository">
    Import repository
  </a>

<a role="menuitem" class="dropdown-item" href="https://gist.github.com/" data-ga-click="Header, create new gist">
  New gist
</a>

  <a role="menuitem" class="dropdown-item" href="/organizations/new" data-ga-click="Header, create new organization">
    New organization
  </a>

  </details-menu>
</details>

    </div>

    <div class="Header-item position-relative mr-0 d-none d-md-flex">
        
  <details class="details-overlay details-reset js-feature-preview-indicator-container" data-feature-preview-indicator-src="/users/mhigginsmoy/feature_preview/indicator_check">

  <summary class="Header-link"
    aria-label="View profile and more"
    data-ga-click="Header, show menu, icon:avatar">

      <span class="feature-preview-indicator js-feature-preview-indicator" style="top: 1px;" hidden></span>
    <span class="dropdown-caret"></span>
  </summary>
  <details-menu class="dropdown-menu dropdown-menu-sw" style="width: 180px" 
      src="/users/11890817/menu" preload>
      <include-fragment>
        <p class="text-center mt-3" data-hide-on-error>
          <svg viewBox="0 0 16 16" fill="none" style="box-sizing: content-box; color: var(--color-icon-primary);" width="32" height="32">
  <circle cx="8" cy="8" r="7" stroke="currentColor" stroke-opacity="0.25" stroke-width="2" vector-effect="non-scaling-stroke" />
  <path d="M15 8a7.002 7.002 0 00-7-7" stroke="currentColor" stroke-width="2" stroke-linecap="round" vector-effect="non-scaling-stroke">
    <animateTransform attributeName="transform" type="rotate" from="0 8 8" to="360 8 8" dur="1s" repeatCount="indefinite" />
  </path>
</svg>
        </p>
        <p class="ml-1 mb-2 mt-2 text-gray-dark" data-show-on-error>
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
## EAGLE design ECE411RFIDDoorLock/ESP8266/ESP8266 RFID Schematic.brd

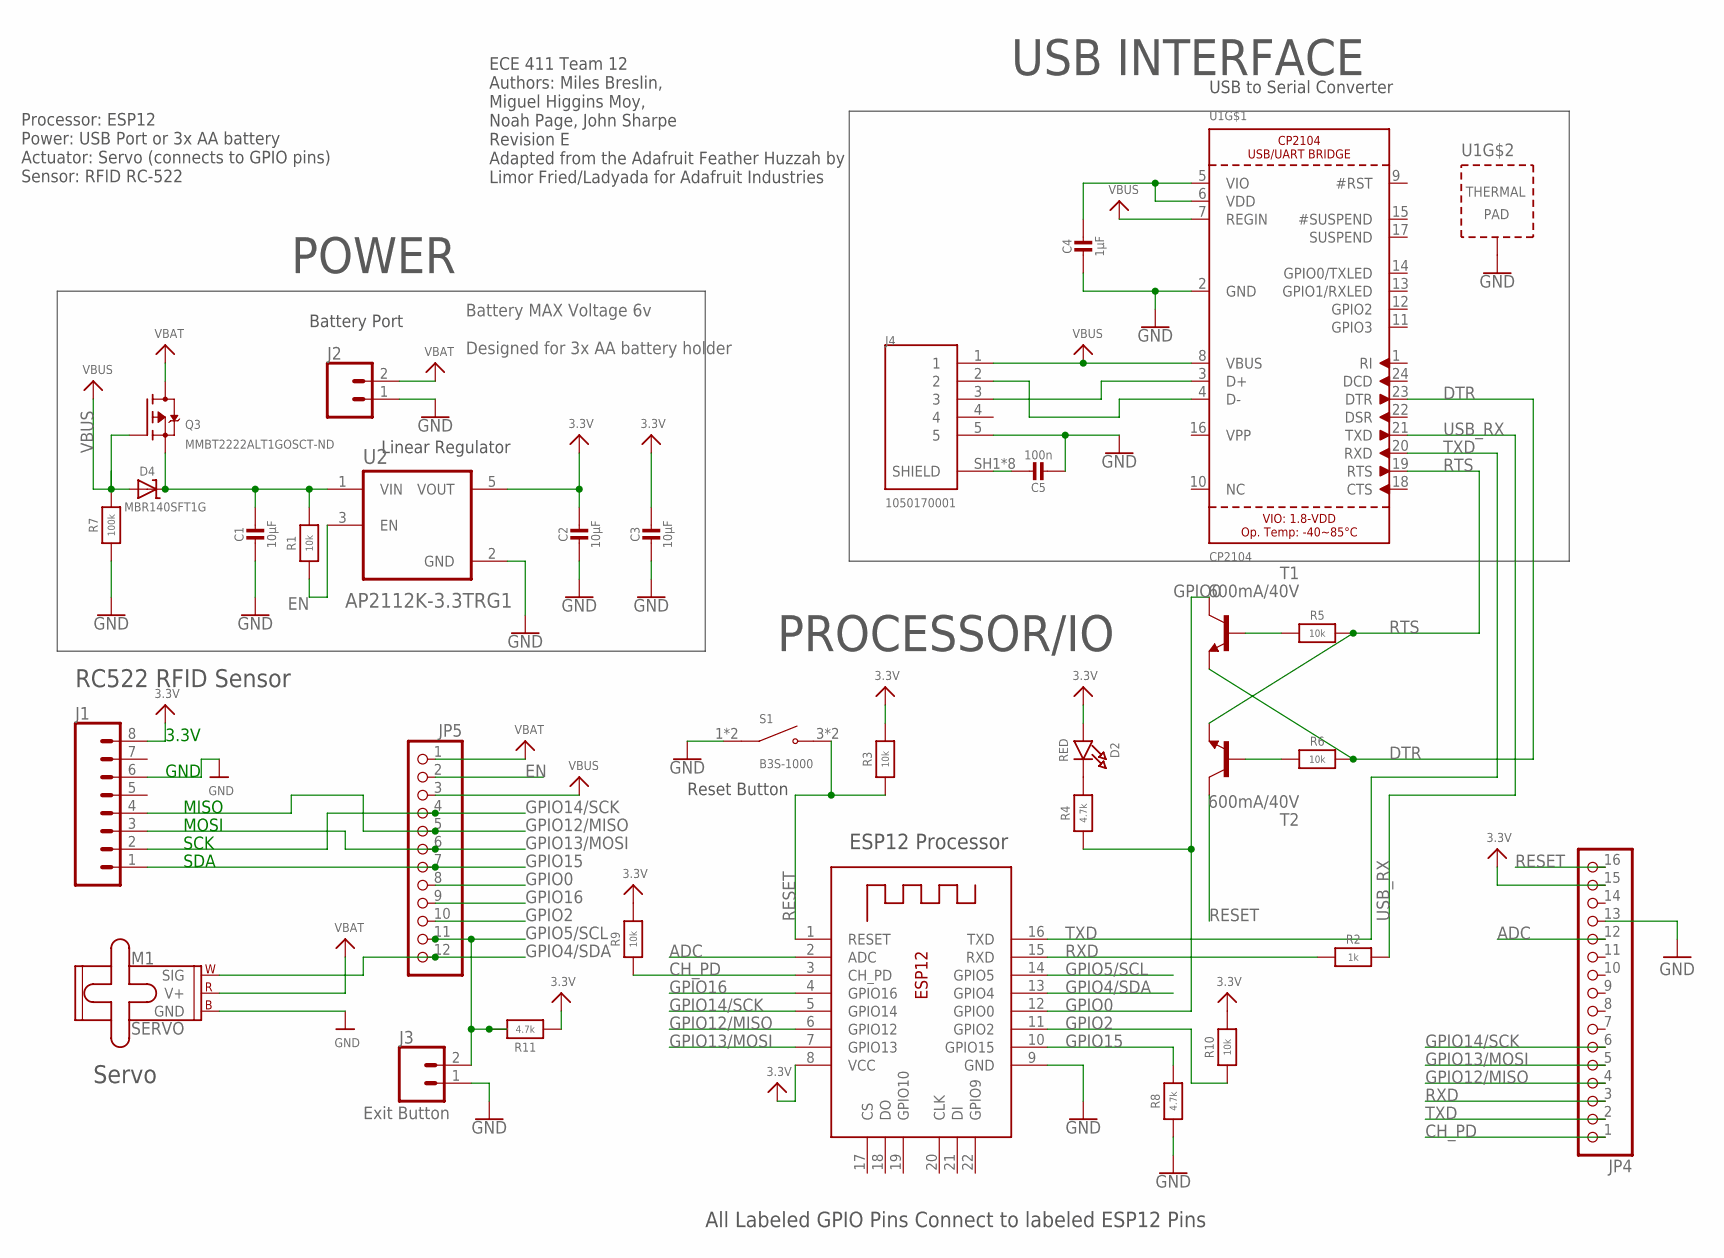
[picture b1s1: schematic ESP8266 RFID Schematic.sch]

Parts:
C1, C2, C3: 10µF; 0603-MINI
C4: 1µF; 0603-MINI
C5: 100n; 0603-MINI
D2: RED; CHIPLED_0603
D4: MBR140SFT1G; SOD-123
J1: CONN_08"; 1X08
J2, J3: CONN_02; 1X02
J4: 1050170001; MOLEX_1050170001
JP4: HEADER-1X16ROUND; 1X16_ROUND
JP5: HEADER-1X12; 1X12_ROUND
M1: SERVO; 1X03
Q3: MMBT2222ALT1GOSCT-ND; SOT23-R
R1, R3, R5, R6, R9, R10: 10k; 0603-MINI
R2: 1k; 0603-MINI
R4, R8, R11: 4.7k; 0603-MINI
R7: 100k; 0603-MINI
S1: B3S-1000; SW_B3S-1000
T1, T2: 600mA/40V; SOT23-3
U1: CP2104; QFN24_4MM_SMSC
U2: AP2112K-3.3TRG1; SOT95P285X140-5N
X1: ESP-12E

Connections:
3.3V: C2.1, C3.1, D2.A, J1.8, JP4.15, R3.2, R9.2, R10.2, R11.1, U2.5 (VOUT), X1.8 (VCC)
ADC: JP4.12, X1.2 (ADC)
CH_PD: JP4.1, R9.1, X1.3 (CH_PD)
DTR: R6.2, T1.2 (E), U1.23 (DTR)
EN: JP5.2, R1.1, U2.3 (EN)
GND: C1.2, C2.2, C3.2, C4.2, C5.2, J1.6, J2.1, J3.1, J4.5, JP4.13, M1.3 (GND), R7.1, R8.1, S1.1 (COM), S1.2 (COM), U1.2 (GND), U1.THERM (TP), U2.2 (GND), X1.9 (GND)
GPIO0: JP5.8, R4.1, T1.3 (C), X1.12 (GPIO0)
GPIO2: JP5.10, R10.1, X1.11 (GPIO2)
GPIO4/SDA: JP5.12, M1.1 (SIG), X1.13 (GPIO4)
GPIO5/SCL: J3.2, JP5.11, R11.2, X1.14 (GPIO5)
GPIO12/MISO: J1.4, JP4.4, JP5.5, X1.6 (GPIO12)
GPIO13/MOSI: J1.3, JP4.5, JP5.6, X1.7 (GPIO13)
GPIO14/SCK: J1.2, JP4.6, JP5.4, X1.5 (GPIO14)
GPIO15: J1.1, JP5.7, R8.2, X1.10 (GPIO15)
GPIO16: JP5.9, X1.4 (GPIO16)
unnamed: C5.1, J4.SH1 (SHIELD), J4.SH2 (SHIELD), J4.SH3 (SHIELD), J4.SH4 (SHIELD), J4.SH5 (SHIELD), J4.SH6 (SHIELD), J4.SH7 (SHIELD), J4.SH8 (SHIELD)
unnamed: J4.3, U1.3 (D+)
unnamed: J4.2, U1.4 (D-)
unnamed: D2.C, R4.2
unnamed: R5.1, T1.1 (B)
unnamed: R6.1, T2.1 (B)
unnamed: C1.1, D4.C, Q3.2 (S), R1.2, U2.1 (VIN)
unnamed: C4.1, U1.5 (VIO), U1.6 (VDD)
RESET: JP4.16, R3.1, S1.3 (NO), S1.4 (NO), T2.3 (C), X1.1 (RESET)
RTS: R5.2, T2.2 (E), U1.19 (RTS)
RXD: JP4.3, R2.1, X1.15 (RXD)
TXD: JP4.2, U1.20 (RXD), X1.16 (TXD)
USB_RX: R2.2, U1.21 (TXD)
VBAT: J2.2, JP5.1, M1.2 (V+), Q3.3 (D)
VBUS: D4.A, J4.1, JP5.3, Q3.1 (G), R7.2, U1.7 (REGIN), U1.8 (VBUS)

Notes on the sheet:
All Labeled GPIO Pins Connect to labeled ESP12 Pins
ESP12 Processor
Reset Button
USB to Serial Converter
Processor: ESP12 Power: USB Port or 3x AA battery Actuator: Servo (connects to GPIO pins) Sensor: RFID RC-522
POWER
USB INTERFACE
PROCESSOR/IO
SDA
SCK
MOSI
MISO
GND
3.3V
RC522 RFID Sensor
Servo
Linear Regulator
Battery Port
ECE 411 Team 12 Authors: Miles Breslin, Miguel Higgins Moy, Noah Page, John Sharpe Revision E Adapted from the Adafruit Feather Huzzah by Limor Fried/Ladyada for Adafruit Industries
Battery MAX Voltage 6v Designed for 3x AA battery holder
Exit Button

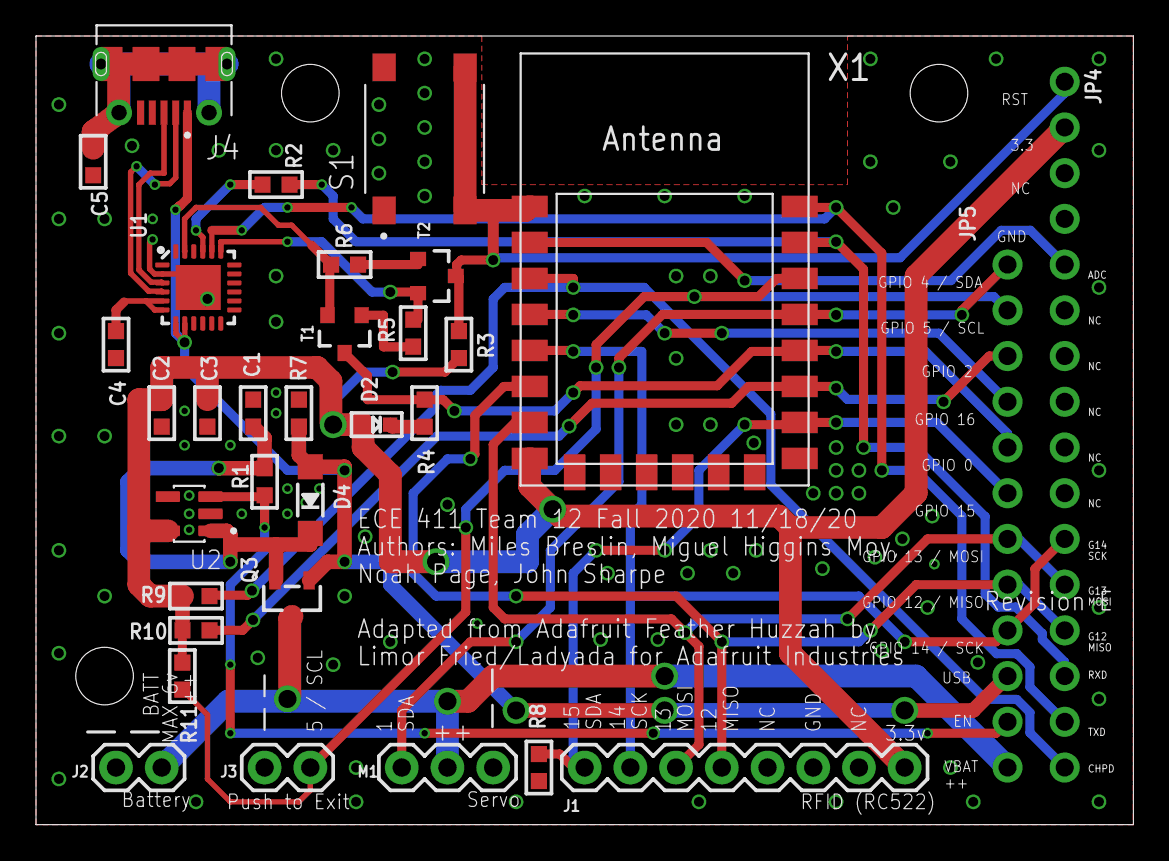
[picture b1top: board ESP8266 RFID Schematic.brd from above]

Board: 2 copper layers, 61.0 x 43.8 mm, 32 parts (0 on the bottom side), 30 nets.

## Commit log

2020-11-08 Moved project Eagle files from main repo
2020-11-09 Update ESP8266 RFID Schematic.brd
    Added servo, RFID sensor, LIPO power port, and better labeling to schematic, did not work on board layout
2020-11-09 First pass at PCB layout
2020-11-09 Traces Routed
2020-11-11 Added some missing component values
2020-11-11 Added and routed resistors R8 - R10 that were missing from original schematic
2020-11-14 cleaned up some of the errors. Need to route 3.3V
2020-11-14 Two ground planes, clean up, and power routing
2020-11-14 added more ground stitching, iso on top pour, info layer on schematic
2020-11-14 routed EN
2020-11-15 Some VIA work and clean up
2020-11-16 Design review feedback changed, USB replaced add new library
2020-11-16 PCB Clean Up from Design Review
2020-11-18 Final PCB Draft, some component modifications, please take a look.
2020-11-18 Final PCB draft
2020-11-21 Added pull up resistor to push to exit
2020-12-09 Readme update and organizing
2021-01-09 Revert
2021-01-09 Fixes and updates
2021-01-09 Readme Fix
2021-01-09 Remove Adafruit Board as reference and added BOM

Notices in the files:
README.md:
Creative Commons Attribution/Share-Alike, all text above must be included in any redistribution. See license.txt for additional details.
parts and their libraries:
SparkFun-Connectors: Licensing: Creative Commons ShareAlike 4.0 International - https://creativecommons.org/licenses/by-sa/4.0
